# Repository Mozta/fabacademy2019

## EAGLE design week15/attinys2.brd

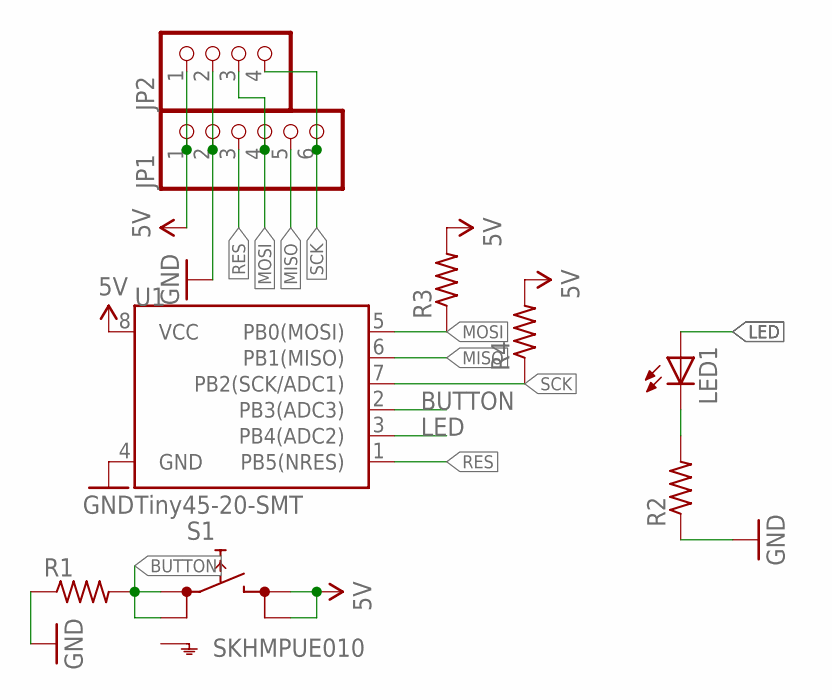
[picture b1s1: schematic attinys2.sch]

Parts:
JP1: PINHD-1X6; 1X06
JP2: PINHD-1X4; 1X04
LED1: LEDSML1206; SML1206
R1, R2, R3, R4: R-US_R1206; R1206
S1: SKHMPUE010; SKHMPXE010
U1: Tiny45-20-SMT; SO08-EIAJ

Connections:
5V: JP1.1, JP2.1, R3.2, R4.2, S1.3 (2.1), S1.4 (2.2), U1.8 (VCC)
BUTTON: R1.2, S1.1 (1.1), S1.2 (1.2), U1.2 (PB3(ADC3))
GND: JP1.2, JP2.2, R1.1, R2.1, U1.4 (GND)
LED: LED1.A, U1.3 (PB4(ADC2))
MISO: JP1.5, U1.6 (PB1(MISO))
MOSI: JP1.4, JP2.3, R3.1, U1.5 (PB0(MOSI))
unnamed: LED1.C, R2.2
RES: JP1.3, U1.1 (PB5(NRES))
SCK: JP1.6, JP2.4, R4.1, U1.7 (PB2(SCK/ADC1))

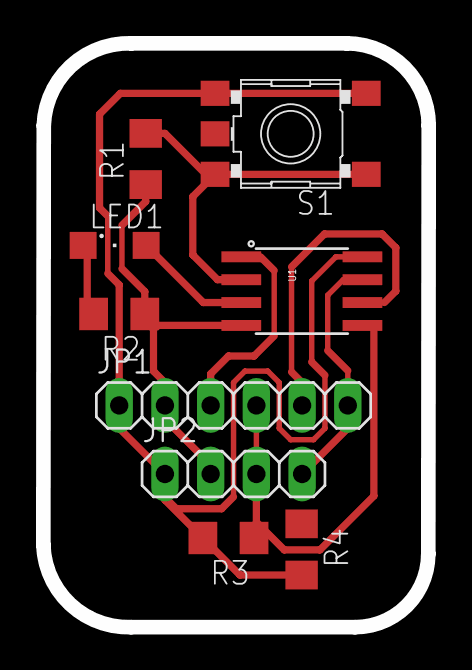
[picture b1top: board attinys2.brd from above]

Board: 2 copper layers, 21.4 x 32.4 mm, 9 parts (0 on the bottom side), 9 nets.

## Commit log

2019-04-30 add files
2019-06-24 clean files
2019-06-24 clean
2019-06-24 Set theme jekyll-theme-hacker

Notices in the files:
parts and their libraries:
SparkFun-DigitalIC: Licensing: Creative Commons ShareAlike 4.0 International - https://creativecommons.org/licenses/by-sa/4.0
